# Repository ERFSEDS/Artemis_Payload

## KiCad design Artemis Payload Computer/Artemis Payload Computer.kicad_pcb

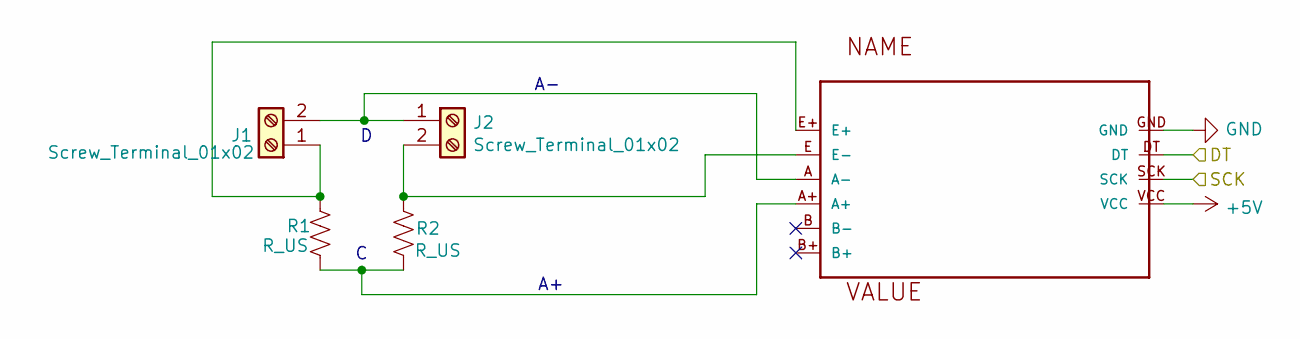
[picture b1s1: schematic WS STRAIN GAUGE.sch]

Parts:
J1, J2: Screw_Terminal_01x02; TerminalBlock_TE_282834-2_1x02_P2.54mm_Horizontal
R1, R2: R_US; R_0603_1608Metric_Pad0.98x0.95mm_HandSolder
U1: HX711

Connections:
+5V: U1.VCC; also elsewhere on the board
/DT: U1.DT; also elsewhere on the board
/SCK: U1.SCK; also elsewhere on the board
GND: U1.GND; also elsewhere on the board
unnamed: J1.1, R1.2, U1.E+
unnamed: J1.2, J2.1, U1.A (A-)
unnamed: J2.2, R2.1, U1.E (E-)
unnamed: R1.1, R2.2, U1.A+

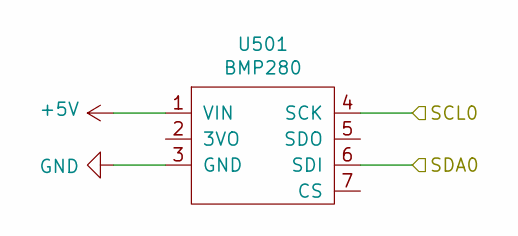
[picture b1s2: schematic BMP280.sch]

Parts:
U501: BMP280

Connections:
+5V: U501.1 (VIN); also elsewhere on the board
/SCL0: U501.4 (SCK); also elsewhere on the board
/SDA0: U501.6 (SDI); also elsewhere on the board
GND: U501.3 (GND); also elsewhere on the board

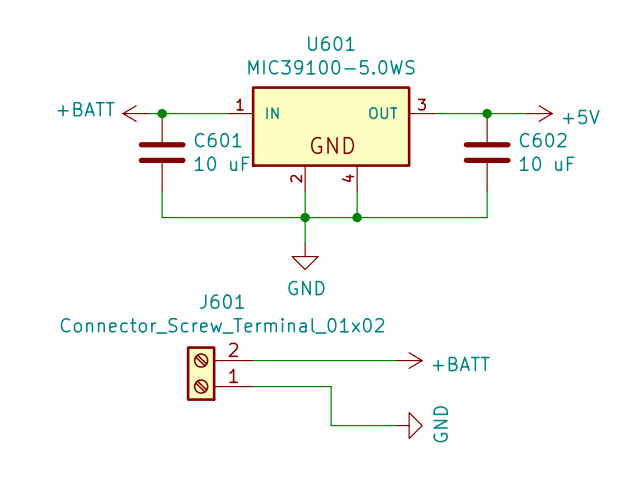
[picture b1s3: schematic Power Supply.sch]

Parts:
C601, C602: 10 uF; C_0603_1608Metric_Pad1.08x0.95mm_HandSolder
J601: Connector_Screw_Terminal_01x02; TerminalBlock_bornier-2_P5.08mm
U601: MIC39100-5.0WS; SOT-223

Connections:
+5V: C602.1, U601.3 (OUT); also elsewhere on the board
+BATT: C601.1, J601.2, U601.1 (IN)
GND: C601.2, C602.2, J601.1, U601.2, U601.4; also elsewhere on the board

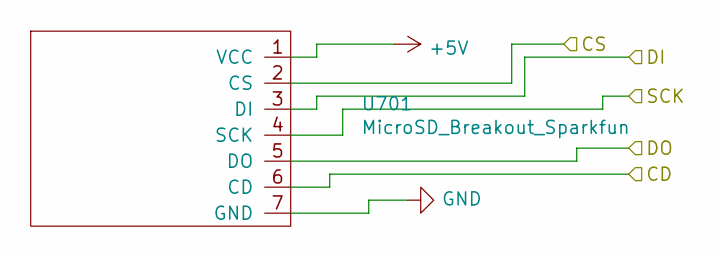
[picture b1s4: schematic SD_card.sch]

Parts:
U701: MicroSD_Breakout_Sparkfun; MicroSD_Breakout

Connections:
+5V: U701.1 (VCC); also elsewhere on the board
/CD: U701.6 (CD); also elsewhere on the board
/CS: U701.2 (CS); also elsewhere on the board
/DI: U701.3 (DI); also elsewhere on the board
/DO: U701.5 (DO); also elsewhere on the board
/SCK: U701.4 (SCK); also elsewhere on the board
GND: U701.7 (GND); also elsewhere on the board

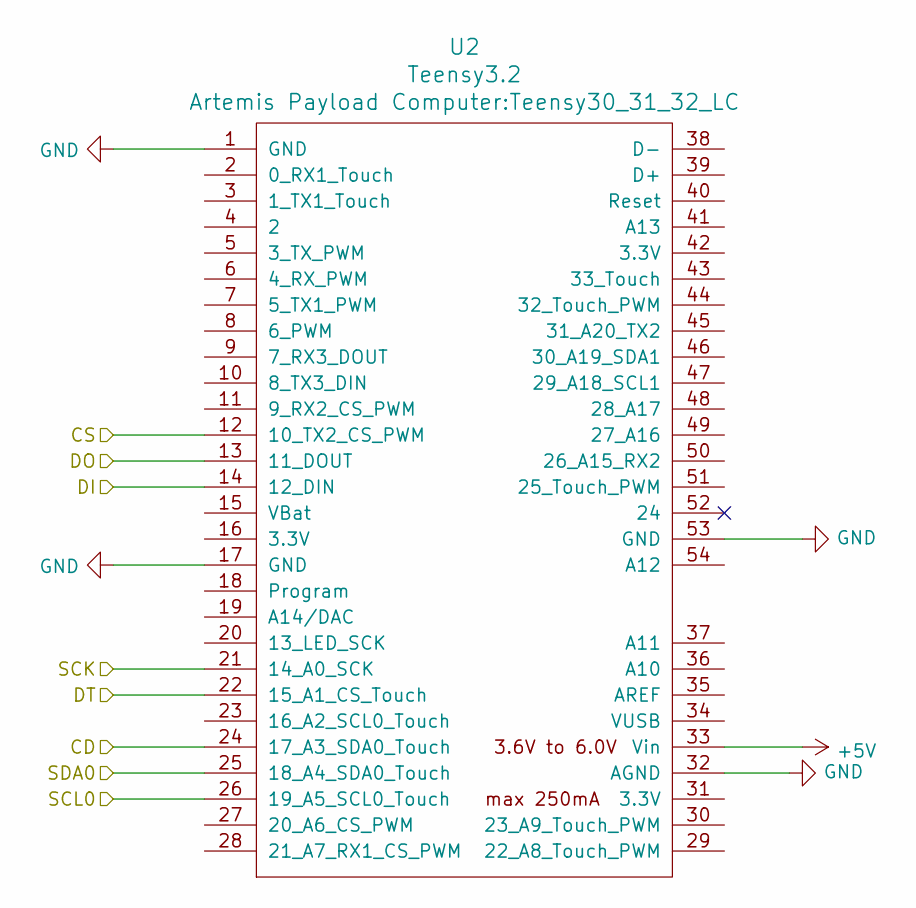
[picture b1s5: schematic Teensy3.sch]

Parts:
U2: Teensy3.2; Teensy30_31_32_LC

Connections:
+5V: U2.33 (Vin); also elsewhere on the board
/CD: U2.24 (17_A3_SDA0_Touch); also elsewhere on the board
/CS: U2.12 (10_TX2_CS_PWM); also elsewhere on the board
/DI: U2.14 (12_DIN); also elsewhere on the board
/DO: U2.13 (11_DOUT); also elsewhere on the board
/DT: U2.22 (15_A1_CS_Touch); also elsewhere on the board
/SCK: U2.21 (14_A0_SCK); also elsewhere on the board
/SCL0: U2.26 (19_A5_SCL0_Touch); also elsewhere on the board
/SDA0: U2.25 (18_A4_SDA0_Touch); also elsewhere on the board
GND: U2.1 (GND), U2.17 (GND), U2.32 (AGND), U2.53 (GND); also elsewhere on the board

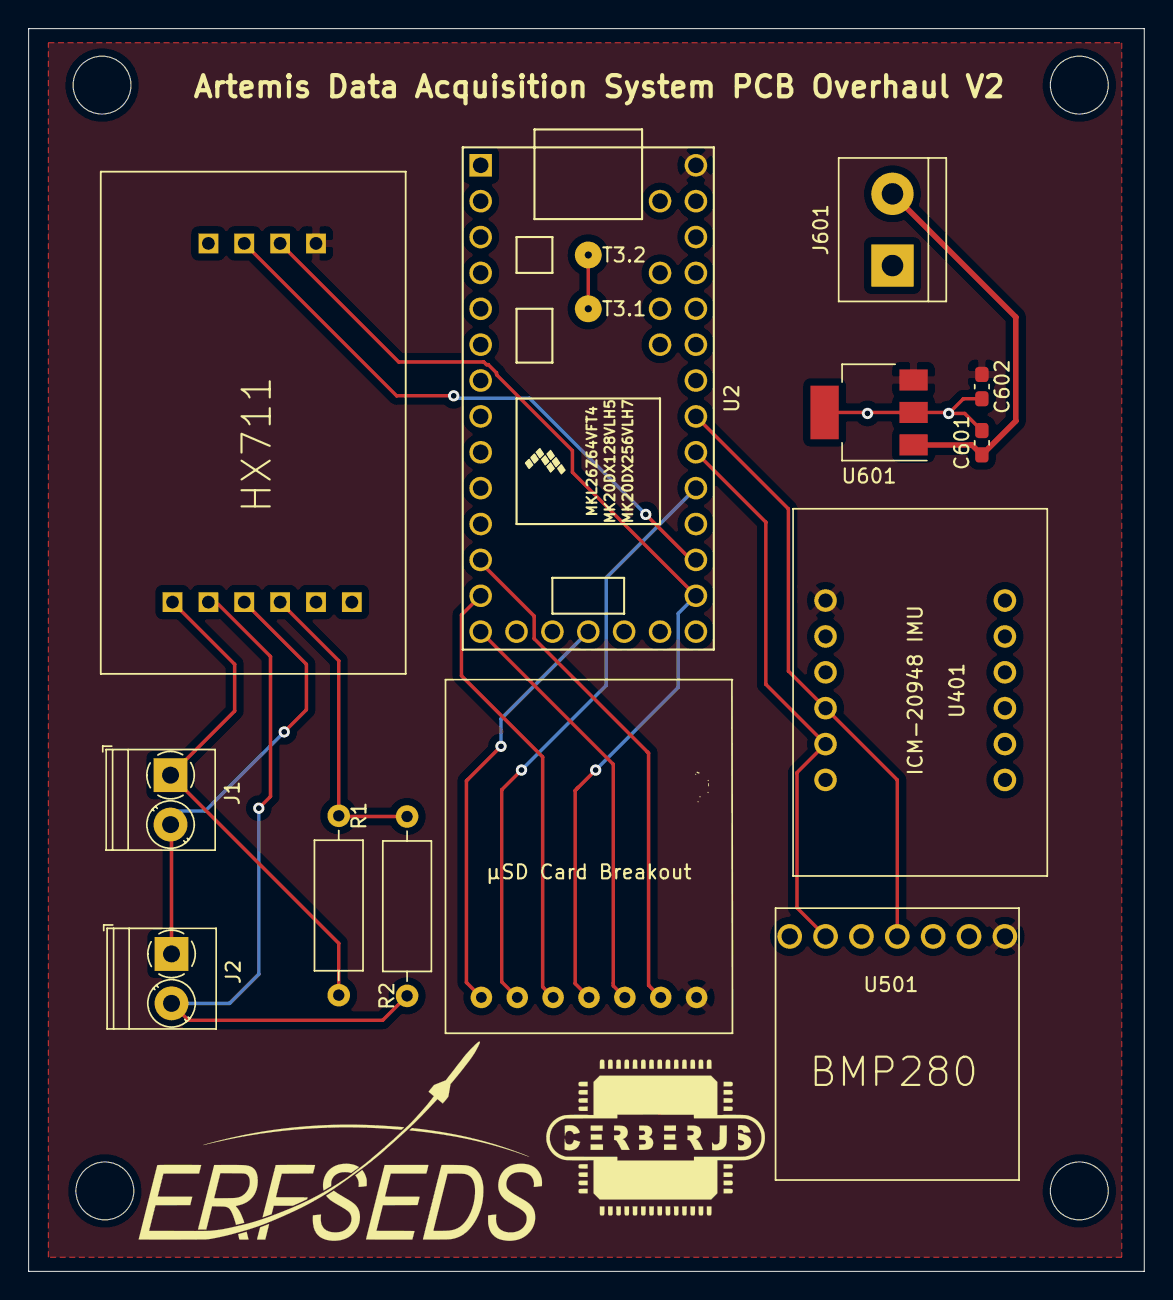
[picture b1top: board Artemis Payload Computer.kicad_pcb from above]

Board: 2 copper layers, 79.0 x 88.0 mm, 13 parts (0 on the bottom side), 15 nets.

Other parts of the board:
U401: ICM-20948

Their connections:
+5V: U401.1; also elsewhere on the board
/SCL0: U401.4; also elsewhere on the board
/SDA0: U401.5; also elsewhere on the board
GND: U401.3; also elsewhere on the board

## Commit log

2021-02-13 Initial KiCad Commit
2021-02-13 Added footprint libraries
2021-02-13 Added Hierarchical sheets. Fixed Symbol Libraries for all users.
2021-02-27 Added BMP280 and IMU to the schematic
2021-02-27 Added Voltage Regulator
2021-03-04 Revert "Added Voltage Regulator"
    This reverts commit e3d7c0c166a86b377dd2931e3fa686f7d92689ce.
2021-03-04 I think I undid this...
2021-03-04 Fuck it we're starting over. Sorry for the mess Nathan
2021-03-04 Added Strain Gauge
2021-03-04 complete redo hehe
2021-03-04 Updated Footprints
2021-03-04 Added PCB Thingy
2021-03-04 Shit
2021-03-04 ready for testing...
2021-03-04 Fixed Strain Gauge Footprint
2021-03-06 big commit, sorry. sd card needs finishing
2021-03-09 Continued work on SD card. Starting PCB layout.
2021-03-09 started tracing... they are bad
2021-03-09 redid layout
2021-03-10 ready for review
2021-03-13 Minor Changes. Approved for ordering
2021-03-15 updated resistor footprint. still ready for ordering
2021-03-29 v2 redesign (layout/sizing fixes)
2021-03-31 adding text, still need to add logos
2021-03-31 logos added
2021-03-31 v2 finalized
